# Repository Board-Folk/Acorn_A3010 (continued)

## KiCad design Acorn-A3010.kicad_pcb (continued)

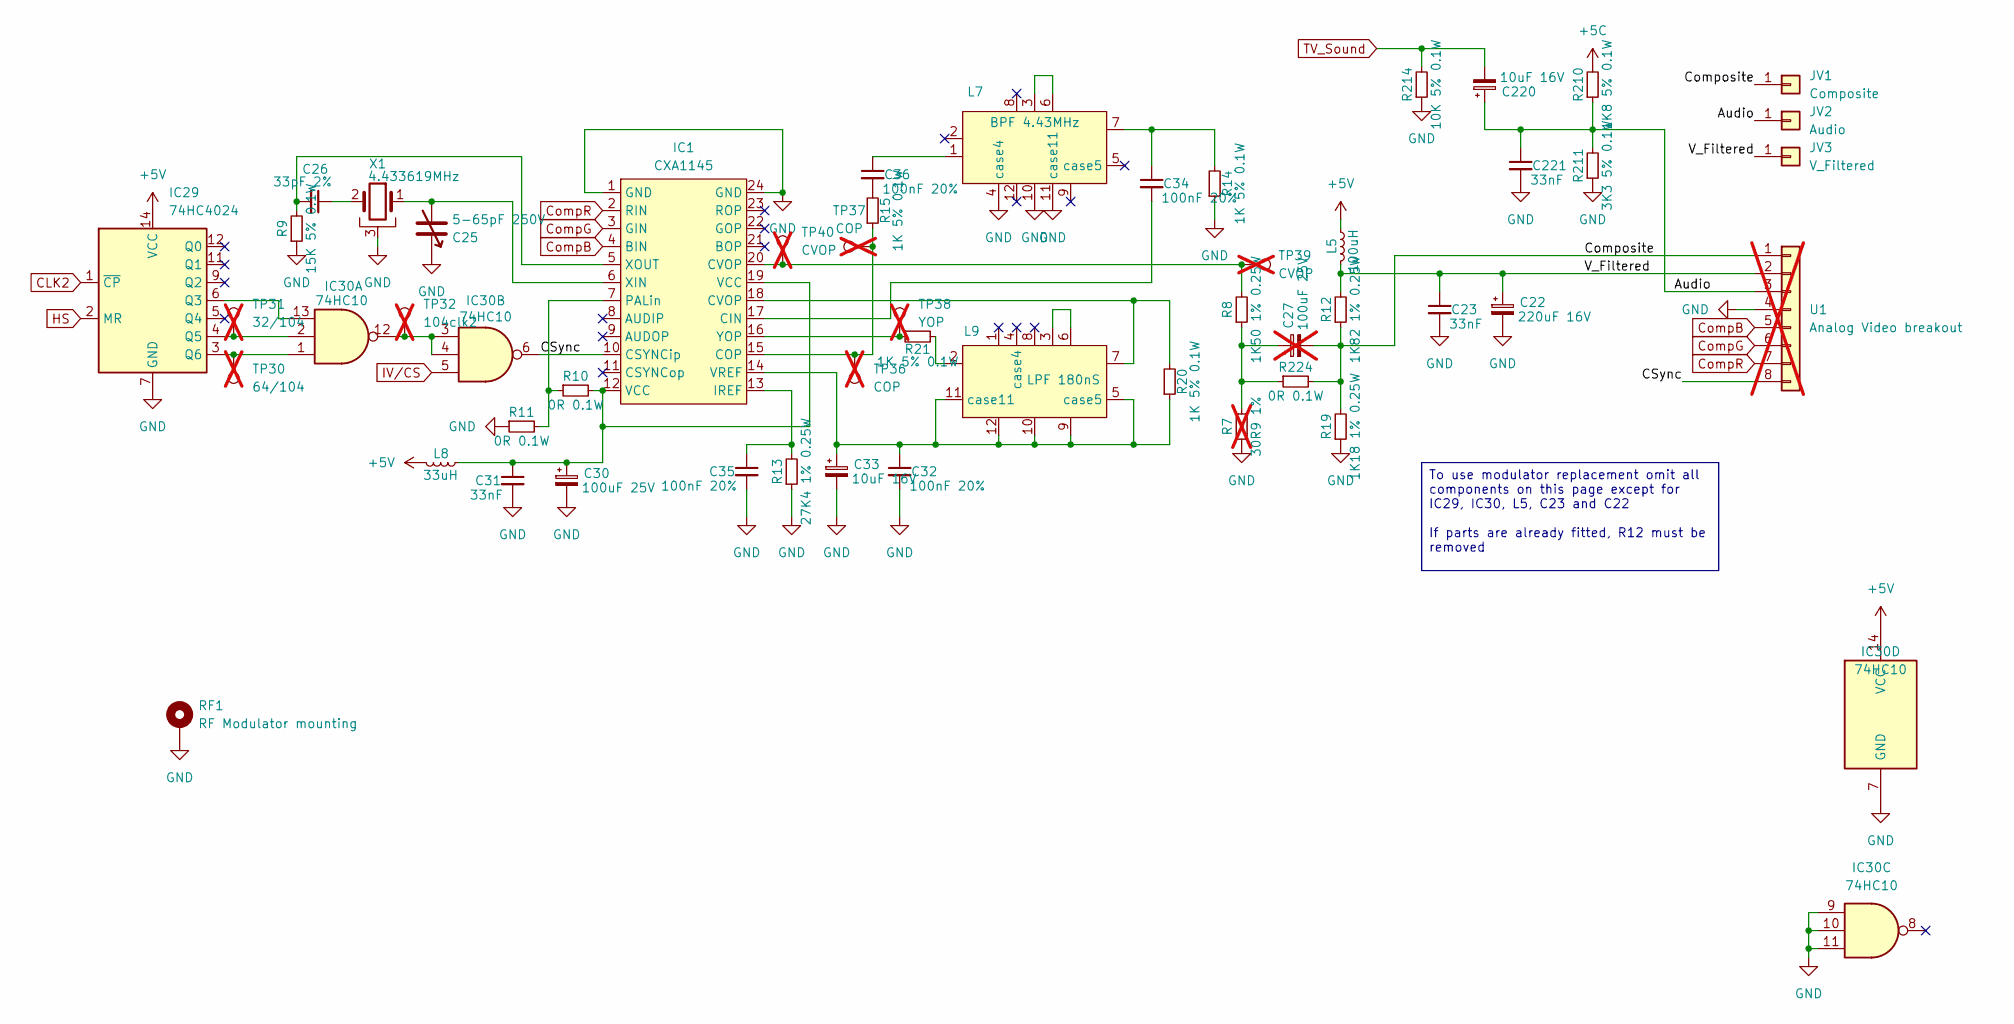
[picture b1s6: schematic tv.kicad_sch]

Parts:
C22: 220uF 16V; CP_Radial_D8.0mm_P5.00mm
C23, C31, C221: 33nF; C_0805_2012Metric; LCSC C344201
C25: 5-65pF 250V; Trim_Capacitor
C26: 33pF 2%; C_0805_2012Metric; LCSC C107115
C27: 100uF 25V; CP_Radial_Tantal_D6.0mm_P5.00mm; not fitted
C30: 100uF 25V; CP_Radial_D8.0mm_P5.00mm
C32, C34, C35, C36: 100nF 20%; C_0805_2012Metric; LCSC C49678
C33: 10uF 16V; CP_Radial_Tantal_D4.5mm_P5.00mm
C220: 10uF 16V; CP_Radial_D5.0mm_P2.50mm
IC1: CXA1145; SOJ-24_7.62x15.875mm_P1.27mm
IC29: 74HC4024; SOIC-14_3.9x8.7mm_P1.27mm; LCSC C2652991
IC30: 74HC10; SOIC-14_3.9x8.7mm_P1.27mm; LCSC C6816
JV1: Composite; PinHeader_1x01_P2.54mm_Vertical
JV2: Audio; PinHeader_1x01_P2.54mm_Vertical
JV3: V_Filtered; PinHeader_1x01_P2.54mm_Vertical
L5: 100uH; L_Axial_L6.6mm_D2.7mm_P10.16mm_Horizontal_Vishay_IM-2
L7: BPF 4.43MHz; BPF4_43M
L8: 33uH; L_Axial_L6.6mm_D2.7mm_P10.16mm_Horizontal_Vishay_IM-2
L9: LPF 180nS; LPF180nS
R7: 30R9 1%; R_1206_3216Metric; LCSC C2960740; not fitted
R8: 1K50 1% 0.25W; R_1206_3216Metric; LCSC C114929
R9: 15K 5% 0.1W; R_0805_2012Metric; LCSC C2933528
R10, R11, R224: 0R 0.1W; R_0805_2012Metric; LCSC C17477
R12: 1K82 1% 0.25W; R_1206_3216Metric; LCSC C844020
R13: 27K4 1% 0.25W; R_1206_3216Metric; LCSC C17477
R14, R15, R20, R21: 1K 5% 0.1W; R_0805_2012Metric; LCSC C2907232
R19: 1K18 1% 0.25W; R_1206_3216Metric; LCSC C422599
R210: 1K8 5% 0.1W; R_0805_2012Metric; LCSC C54102237
R211: 3K3 5% 0.1W; R_0805_2012Metric; LCSC C2930266
R214: 10K 5% 0.1W; R_0805_2012Metric; LCSC C2907219
RF1: RF Modulator mounting; Rf Modulator
TP30: 64/104; TestPoint_Pad_D1.0mm; not fitted
TP31: 32/104; TestPoint_Pad_D1.0mm; not fitted
TP32: 104clk2; TestPoint_Pad_D1.0mm; not fitted
TP36, TP37: COP; TestPoint_Pad_D1.0mm; not fitted
TP38: YOP; TestPoint_Pad_D1.0mm; not fitted
TP39, TP40: CVOP; TestPoint_Pad_D1.0mm; not fitted
U1: Analog Video breakout; PinSocket_1x08_P2.54mm_Vertical; not fitted
X1: 4.433619MHz; Crystal_HC49-U_Horizontal_1EP_style2

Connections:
+5C: R210.2; also elsewhere on the board
+5V: IC29.14 (VCC), IC30.14 (VCC), L5.1, L8.2; also elsewhere on the board
/Analog Video/Audio: C220.1, C221.1, JV2.1, R210.1, R211.2, U1.3
/Analog Video/CSync: IC1.10 (CSYNCip), IC30.6, U1.8
/Analog Video/Composite: C27.2, JV1.1, R12.1, R19.2, R224.2, U1.1
/Analog Video/V_Filtered: C22.1, C23.1, JV3.1, L5.2, R12.2, U1.2
CLK2: IC29.1 (~CP); also elsewhere on the board
CompB: IC1.4 (BIN), U1.5; also elsewhere on the board
CompG: IC1.3 (GIN), U1.6; also elsewhere on the board
CompR: IC1.2 (RIN), U1.7; also elsewhere on the board
GND: C22.2, C23.2, C25.1, C30.2, C31.2, C32.2, C33.2, C35.2, C221.2, IC1.1 (GND), IC1.24 (GND), IC29.7 (GND), IC30.7 (GND), IC30.9, IC30.10, IC30.11, L7.4 (case4), L7.10, L7.11 (case11), R7.1, R9.1, R11.1, R13.1, R14.1, R19.1, R211.1, R214.1, RF1.1, U1.4, X1.3; also elsewhere on the board
HS: IC29.2 (MR); also elsewhere on the board
IV/CS: IC30.5; also elsewhere on the board
unnamed: C26.1, X1.2
unnamed: C27.1, R7.2, R8.1, R224.1
unnamed: C30.1, C31.1, IC1.12 (VCC), IC1.19 (VCC), L8.1, R10.2
unnamed: C34.1, L7.7, R14.2
unnamed: C36.1, L7.1
unnamed: C36.2, R15.2
unnamed: C34.2, IC1.17 (CIN)
unnamed: IC1.15 (COP), R15.1, TP36.1, TP37.1
unnamed: IC1.18 (CVOP), L9.7, R20.2
unnamed: IC1.20 (CVOP), R8.2, TP39.1, TP40.1
unnamed: C35.1, IC1.13 (IREF), R13.2
unnamed: IC1.7 (PALin), R10.1, R11.2
unnamed: C32.1, C33.1, IC1.14 (VREF), L9.5 (case5), L9.9, L9.10, L9.11 (case11), L9.12, R20.1
unnamed: C25.2, IC1.6 (XIN), X1.1
unnamed: C26.2, IC1.5 (XOUT), R9.2
unnamed: IC1.16 (YOP), R21.1, TP38.1
unnamed: IC29.6 (Q3), IC30.13
unnamed: IC29.4 (Q5), IC30.2, TP31.1
unnamed: IC29.3 (Q6), IC30.1, TP30.1
unnamed: IC30.3, IC30.4, IC30.12, TP32.1
unnamed: L7.3, L7.6
unnamed: L9.2, R21.2
unnamed: L9.3, L9.6
TV_Sound: C220.2, R214.2; also elsewhere on the board

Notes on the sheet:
To use modulator replacement omit all components on this page except for IC29, IC30, L5, C23 and C22 If parts are already fitted, R12 must be removed

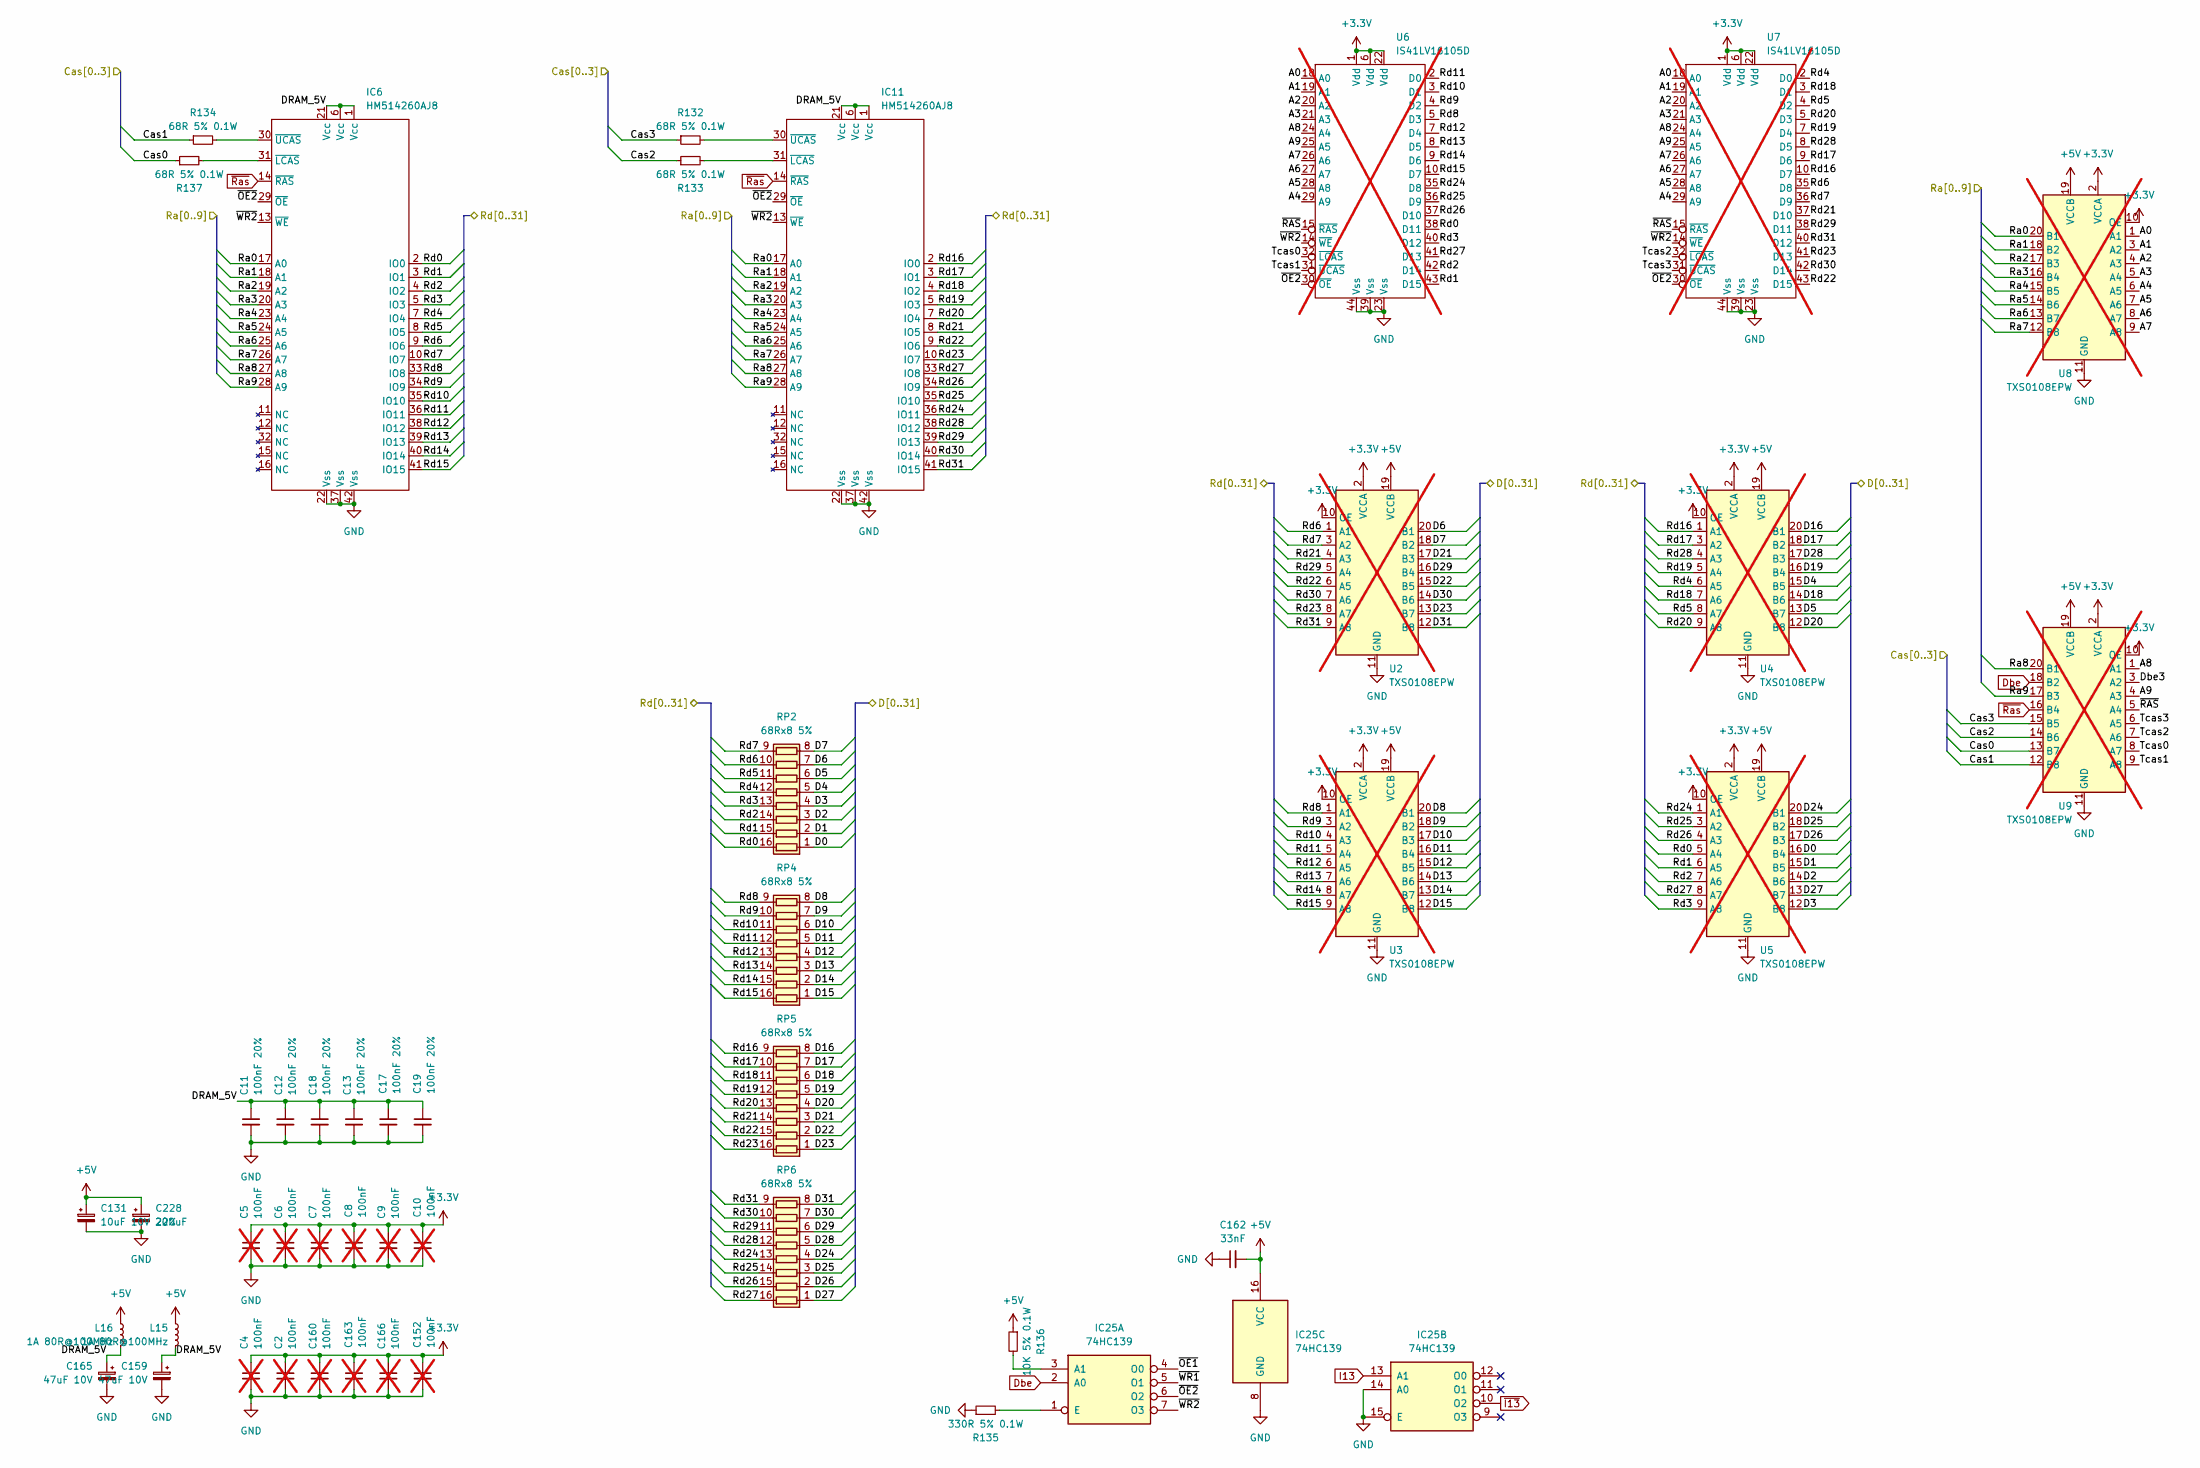
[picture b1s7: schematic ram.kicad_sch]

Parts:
C2, C4, C5, C6, C7, C8, C9, C10, C152, C160, C163, C166: 100nF; C_0805_2012Metric; LCSC C49678; not fitted
C11, C12, C13, C17, C18, C19: 100nF 20%; C_0805_2012Metric; LCSC C49678
C131: 10uF 10V 20%; CP_Radial_Tantal_D7.0mm_P5.00mm
C159, C165: 47uF 10V; CP_Axial_L11.0mm_D6.0mm_P18.00mm_Horizontal
C162: 33nF; C_0805_2012Metric; LCSC C49678
C228: 220uF; CP_Radial_D8.0mm_P5.00mm
IC6, IC11: HM514260AJ8; SOJ-42_10.16mm_P1.27mm
IC25: 74HC139; SOIC-16_3.9x9.9mm_P1.27mm; LCSC C7494
L15, L16: 1A 80R@100MHz; L_Acorn_8x3mm
R132, R133, R134, R137: 68R 5% 0.1W; R_0805_2012Metric
R135: 330R 5% 0.1W; R_0805_2012Metric; LCSC C17630
R136: 10K 5% 0.1W; R_0805_2012Metric; LCSC C2907219
RP2, RP4, RP5, RP6: 68Rx8 5%; SOIC-16W_5.3x10.2mm_P1.27mm; LCSC C1739978
U2, U3, U4, U5, U8, U9: TXS0108EPW; TSSOP-20_4.4x6.5mm_P0.65mm; LCSC C17206; not fitted
U6, U7: IS41LV16105D; TSOP-II-44-50; not fitted

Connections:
+5V: C131.1, C162.2, C228.1, IC25.16 (VCC), L15.1, L16.1, R136.1, U2.19 (VCCB), U3.19 (VCCB), U4.19 (VCCB), U5.19 (VCCB), U8.19 (VCCB), U9.19 (VCCB); also elsewhere on the board
/CPU/Cas0: R137.1, U9.13 (B7); also elsewhere on the board
/CPU/Cas1: R134.1, U9.12 (B8); also elsewhere on the board
/CPU/Cas2: R133.1, U9.14 (B6); also elsewhere on the board
/CPU/Cas3: R132.1, U9.15 (B5); also elsewhere on the board
/CPU/D0: RP2.1 (R1.1), U5.16 (B4); also elsewhere on the board
/CPU/D1: RP2.2 (R2.1), U5.15 (B5); also elsewhere on the board
/CPU/D2: RP2.3 (R3.1), U5.14 (B6); also elsewhere on the board
/CPU/D3: RP2.4 (R4.1), U5.12 (B8); also elsewhere on the board
/CPU/D4: RP2.5 (R5.1), U4.15 (B5); also elsewhere on the board
/CPU/D5: RP2.6 (R6.1), U4.13 (B7); also elsewhere on the board
/CPU/D6: RP2.7 (R7.1), U2.20 (B1); also elsewhere on the board
/CPU/D7: RP2.8 (R8.1), U2.18 (B2); also elsewhere on the board
/CPU/D8: RP4.8 (R8.1), U3.20 (B1); also elsewhere on the board
/CPU/D9: RP4.7 (R7.1), U3.18 (B2); also elsewhere on the board
/CPU/D10: RP4.6 (R6.1), U3.17 (B3); also elsewhere on the board
/CPU/D11: RP4.5 (R5.1), U3.16 (B4); also elsewhere on the board
/CPU/D12: RP4.4 (R4.1), U3.15 (B5); also elsewhere on the board
/CPU/D13: RP4.3 (R3.1), U3.14 (B6); also elsewhere on the board
/CPU/D14: RP4.2 (R2.1), U3.13 (B7); also elsewhere on the board
/CPU/D15: RP4.1 (R1.1), U3.12 (B8); also elsewhere on the board
/CPU/D16: RP5.8 (R8.1), U4.20 (B1); also elsewhere on the board
/CPU/D17: RP5.7 (R7.1), U4.18 (B2); also elsewhere on the board
/CPU/D18: RP5.6 (R6.1), U4.14 (B6); also elsewhere on the board
/CPU/D19: RP5.5 (R5.1), U4.16 (B4); also elsewhere on the board
/CPU/D20: RP5.4 (R4.1), U4.12 (B8); also elsewhere on the board
/CPU/D21: RP5.3 (R3.1), U2.17 (B3); also elsewhere on the board
/CPU/D22: RP5.2 (R2.1), U2.15 (B5); also elsewhere on the board
/CPU/D23: RP5.1 (R1.1), U2.13 (B7); also elsewhere on the board
/CPU/D24: RP6.4 (R4.1), U5.20 (B1); also elsewhere on the board
/CPU/D25: RP6.3 (R3.1), U5.18 (B2); also elsewhere on the board
/CPU/D26: RP6.2 (R2.1), U5.17 (B3); also elsewhere on the board
/CPU/D27: RP6.1 (R1.1), U5.13 (B7); also elsewhere on the board
/CPU/D28: RP6.5 (R5.1), U4.17 (B3); also elsewhere on the board
/CPU/D29: RP6.6 (R6.1), U2.16 (B4); also elsewhere on the board
/CPU/D30: RP6.7 (R7.1), U2.14 (B6); also elsewhere on the board
/CPU/D31: RP6.8 (R8.1), U2.12 (B8); also elsewhere on the board
/CPU/Ra0: IC6.17 (A0), IC11.17 (A0), U8.20 (B1); also elsewhere on the board
/CPU/Ra1: IC6.18 (A1), IC11.18 (A1), U8.18 (B2); also elsewhere on the board
/CPU/Ra2: IC6.19 (A2), IC11.19 (A2), U8.17 (B3); also elsewhere on the board
/CPU/Ra3: IC6.20 (A3), IC11.20 (A3), U8.16 (B4); also elsewhere on the board
/CPU/Ra4: IC6.23 (A4), IC11.23 (A4), U8.15 (B5); also elsewhere on the board
/CPU/Ra5: IC6.24 (A5), IC11.24 (A5), U8.14 (B6); also elsewhere on the board
/CPU/Ra6: IC6.25 (A6), IC11.25 (A6), U8.13 (B7); also elsewhere on the board
/CPU/Ra7: IC6.26 (A7), IC11.26 (A7), U8.12 (B8); also elsewhere on the board
/CPU/Ra8: IC6.27 (A8), IC11.27 (A8), U9.20 (B1); also elsewhere on the board
/CPU/Ra9: IC6.28 (A9), IC11.28 (A9), U9.17 (B3); also elsewhere on the board
/RAM/DRAM_5V: C11.1, C12.1, C13.1, C17.1, C18.1, C19.1, C159.1, C165.1, IC6.1 (Vcc), IC6.6 (Vcc), IC6.21 (Vcc), IC11.1 (Vcc), IC11.6 (Vcc), IC11.21 (Vcc), L15.2, L16.2
/RAM/Rd0: IC6.2 (IO0), RP2.16 (R1.2), U5.5 (A4), U6.38 (D11)
/RAM/Rd1: IC6.3 (IO1), RP2.15 (R2.2), U5.6 (A5), U6.43 (D15)
/RAM/Rd2: IC6.4 (IO2), RP2.14 (R3.2), U5.7 (A6), U6.42 (D14)
/RAM/Rd3: IC6.5 (IO3), RP2.13 (R4.2), U5.9 (A8), U6.40 (D12)
/RAM/Rd4: IC6.7 (IO4), RP2.12 (R5.2), U4.6 (A5), U7.2 (D0)
/RAM/Rd5: IC6.8 (IO5), RP2.11 (R6.2), U4.8 (A7), U7.4 (D2)
/RAM/Rd6: IC6.9 (IO6), RP2.10 (R7.2), U2.1 (A1), U7.35 (D8)
/RAM/Rd7: IC6.10 (IO7), RP2.9 (R8.2), U2.3 (A2), U7.36 (D9)
/RAM/Rd8: IC6.33 (IO8), RP4.9 (R8.2), U3.1 (A1), U6.5 (D3)
/RAM/Rd9: IC6.34 (IO9), RP4.10 (R7.2), U3.3 (A2), U6.4 (D2)
/RAM/Rd10: IC6.35 (IO10), RP4.11 (R6.2), U3.4 (A3), U6.3 (D1)
/RAM/Rd11: IC6.36 (IO11), RP4.12 (R5.2), U3.5 (A4), U6.2 (D0)
/RAM/Rd12: IC6.38 (IO12), RP4.13 (R4.2), U3.6 (A5), U6.7 (D4)
/RAM/Rd13: IC6.39 (IO13), RP4.14 (R3.2), U3.7 (A6), U6.8 (D5)
/RAM/Rd14: IC6.40 (IO14), RP4.15 (R2.2), U3.8 (A7), U6.9 (D6)
/RAM/Rd15: IC6.41 (IO15), RP4.16 (R1.2), U3.9 (A8), U6.10 (D7)
/RAM/Rd16: IC11.2 (IO0), RP5.9 (R8.2), U4.1 (A1), U7.10 (D7)
/RAM/Rd17: IC11.3 (IO1), RP5.10 (R7.2), U4.3 (A2), U7.9 (D6)
/RAM/Rd18: IC11.4 (IO2), RP5.11 (R6.2), U4.7 (A6), U7.3 (D1)
/RAM/Rd19: IC11.5 (IO3), RP5.12 (R5.2), U4.5 (A4), U7.7 (D4)
/RAM/Rd20: IC11.7 (IO4), RP5.13 (R4.2), U4.9 (A8), U7.5 (D3)
/RAM/Rd21: IC11.8 (IO5), RP5.14 (R3.2), U2.4 (A3), U7.37 (D10)
/RAM/Rd22: IC11.9 (IO6), RP5.15 (R2.2), U2.6 (A5), U7.43 (D15)
/RAM/Rd23: IC11.10 (IO7), RP5.16 (R1.2), U2.8 (A7), U7.41 (D13)
/RAM/Rd24: IC11.36 (IO11), RP6.13 (R4.2), U5.1 (A1), U6.35 (D8)
/RAM/Rd25: IC11.35 (IO10), RP6.14 (R3.2), U5.3 (A2), U6.36 (D9)
/RAM/Rd26: IC11.34 (IO9), RP6.15 (R2.2), U5.4 (A3), U6.37 (D10)
/RAM/Rd27: IC11.33 (IO8), RP6.16 (R1.2), U5.8 (A7), U6.41 (D13)
/RAM/Rd28: IC11.38 (IO12), RP6.12 (R5.2), U4.4 (A3), U7.8 (D5)
/RAM/Rd29: IC11.39 (IO13), RP6.11 (R6.2), U2.5 (A4), U7.38 (D11)
/RAM/Rd30: IC11.40 (IO14), RP6.10 (R7.2), U2.7 (A6), U7.42 (D14)
/RAM/Rd31: IC11.41 (IO15), RP6.9 (R8.2), U2.9 (A8), U7.40 (D12)
/RAM/~OE1: IC25.4 (O0)
/RAM/~OE2: IC6.29 (~OE), IC11.29 (~OE), IC25.6 (O2), U6.30 (~OE), U7.30 (~OE)
/RAM/~WR1: IC25.5 (O1)
/RAM/~WR2: IC6.13 (~WE), IC11.13 (~WE), IC25.7 (O3), U6.14 (~WE), U7.14 (~WE)
Dbe: IC25.2 (A0), U9.18 (B2); also elsewhere on the board
GND: C2.2, C4.2, C5.2, C6.2, C7.2, C8.2, C9.2, C10.2, C11.2, C12.2, C13.2, C17.2, C18.2, C19.2, C131.2, C152.2, C159.2, C160.2, C162.1, C163.2, C165.2, C166.2, C228.2, IC6.22 (Vss), IC6.37 (Vss), IC6.42 (Vss), IC11.22 (Vss), IC11.37 (Vss), IC11.42 (Vss), IC25.8 (GND), IC25.14 (A0), IC25.15 (E), R135.1, U2.11 (GND), U3.11 (GND), U4.11 (GND), U5.11 (GND), U6.23 (Vss), U6.39 (Vss), U6.44 (Vss), U7.23 (Vss), U7.39 (Vss), U7.44 (Vss), U8.11 (GND), U9.11 (GND); also elsewhere on the board
I13: IC25.13 (A1); also elsewhere on the board
unnamed: C2.1, C4.1, C5.1, C6.1, C7.1, C8.1, C9.1, C10.1, C152.1, C160.1, C163.1, C166.1, U2.2 (VCCA), U2.10 (OE), U3.2 (VCCA), U3.10 (OE), U4.2 (VCCA), U4.10 (OE), U5.2 (VCCA), U5.10 (OE), U6.1 (Vdd), U6.6 (Vdd), U6.22 (Vdd), U7.1 (Vdd), U7.6 (Vdd), U7.22 (Vdd), U8.2 (VCCA), U8.10 (OE), U9.2 (VCCA), U9.10 (OE)
unnamed: IC6.31 (~LCAS), R137.2
unnamed: IC6.30 (~UCAS), R134.2
unnamed: IC11.31 (~LCAS), R133.2
unnamed: IC11.30 (~UCAS), R132.2
unnamed: IC25.3 (A1), R136.2
unnamed: IC25.1 (E), R135.2
unnamed: U6.11 (NC), U6.12 (NC), U6.13 (NC), U6.16 (NC), U6.17 (NC), U6.33 (NC), U6.34 (NC)
unnamed: U6.15 (~RAS), U7.15 (~RAS), U9.5 (A4)
unnamed: U6.18 (A0), U7.18 (A0), U8.1 (A1)
unnamed: U6.19 (A1), U7.19 (A1), U8.3 (A2)
unnamed: U6.20 (A2), U7.20 (A2), U8.4 (A3)
unnamed: U6.21 (A3), U7.21 (A3), U8.5 (A4)
unnamed: U6.24 (A4), U7.24 (A4), U9.1 (A1)
unnamed: U6.25 (A5), U7.25 (A5), U9.4 (A3)
unnamed: U6.26 (A6), U7.26 (A6), U8.9 (A8)
unnamed: U6.27 (A7), U7.27 (A7), U8.8 (A7)
unnamed: U6.28 (A8), U7.28 (A8), U8.7 (A6)
unnamed: U6.29 (A9), U7.29 (A9), U8.6 (A5)
unnamed: U6.31 (~UCAS), U9.9 (A8)
unnamed: U6.32 (~LCAS), U9.8 (A7)
unnamed: U7.11 (NC), U7.12 (NC), U7.13 (NC), U7.16 (NC), U7.17 (NC), U7.33 (NC), U7.34 (NC)
unnamed: U7.31 (~UCAS), U9.6 (A5)
unnamed: U7.32 (~LCAS), U9.7 (A6)
~I13: IC25.10 (O2); also elsewhere on the board
~Ras: IC6.14 (~RAS), IC11.14 (~RAS), U9.16 (B4); also elsewhere on the board

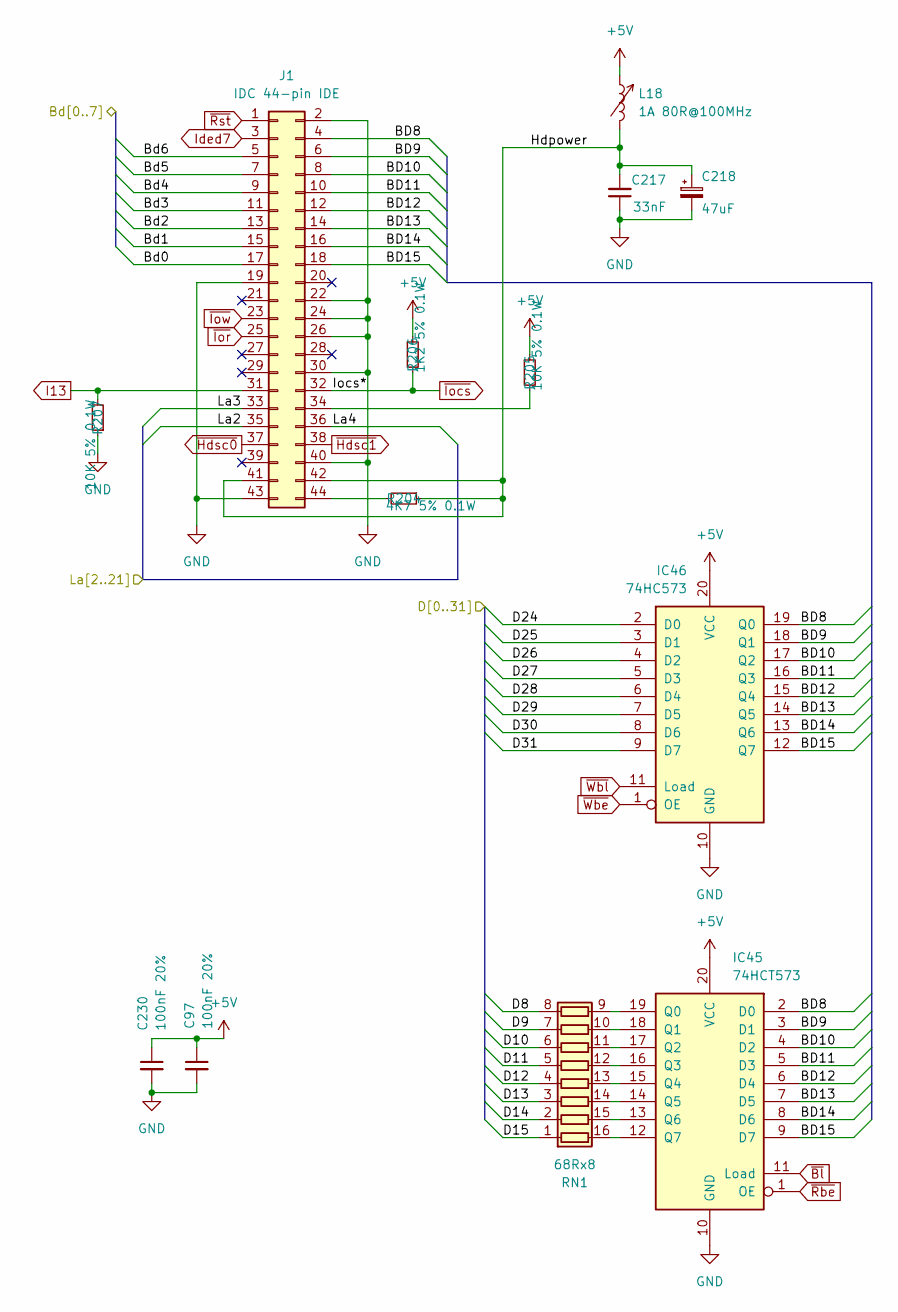
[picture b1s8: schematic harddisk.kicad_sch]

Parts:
C97, C230: 100nF 20%; C_0805_2012Metric; LCSC C49678
C217: 33nF; C_0805_2012Metric; LCSC C344201
C218: 47uF; CP_Radial_D8.0mm_P5.00mm
IC45: 74HCT573; SOP-20_7.5x12.8mm_P1.27mm; LCSC C52145555
IC46: 74HC573; SOP-20_7.5x12.8mm_P1.27mm; LCSC C55388
J1: IDC 44-pin IDE; PinHeader_2x22_P2.00mm_Vertical
L18: 1A 80R@100MHz; L_Acorn_8x3mm
R204: 4K7 5% 0.1W; R_0805_2012Metric; LCSC C2907326
R205: 10K 5% 0.1W; R_0805_2012Metric; LCSC C2907219
R206: 1K2 5% 0.1W; R_0805_2012Metric; LCSC C2933293
R207: 10K 5% 0.1W; R_0805_2012Metric
RN1: 68Rx8; SOIC-16W_5.3x10.2mm_P1.27mm; LCSC C1739978

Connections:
+5V: C97.1, C230.1, IC45.20 (VCC), IC46.20 (VCC), L18.1, R205.1, R206.1; also elsewhere on the board
/CPU/Bd0: J1.17; also elsewhere on the board
/CPU/Bd1: J1.15; also elsewhere on the board
/CPU/Bd2: J1.13; also elsewhere on the board
/CPU/Bd3: J1.11; also elsewhere on the board
/CPU/Bd4: J1.9; also elsewhere on the board
/CPU/Bd5: J1.7; also elsewhere on the board
/CPU/Bd6: J1.5; also elsewhere on the board
/CPU/D8: RN1.8 (R8.1); also elsewhere on the board
/CPU/D9: RN1.7 (R7.1); also elsewhere on the board
/CPU/D10: RN1.6 (R6.1); also elsewhere on the board
/CPU/D11: RN1.5 (R5.1); also elsewhere on the board
/CPU/D12: RN1.4 (R4.1); also elsewhere on the board
/CPU/D13: RN1.3 (R3.1); also elsewhere on the board
/CPU/D14: RN1.2 (R2.1); also elsewhere on the board
/CPU/D15: RN1.1 (R1.1); also elsewhere on the board
/CPU/D24: IC46.2 (D0); also elsewhere on the board
/CPU/D25: IC46.3 (D1); also elsewhere on the board
/CPU/D26: IC46.4 (D2); also elsewhere on the board
/CPU/D27: IC46.5 (D3); also elsewhere on the board
/CPU/D28: IC46.6 (D4); also elsewhere on the board
/CPU/D29: IC46.7 (D5); also elsewhere on the board
/CPU/D30: IC46.8 (D6); also elsewhere on the board
/CPU/D31: IC46.9 (D7); also elsewhere on the board
/CPU/La2: J1.35; also elsewhere on the board
/CPU/La3: J1.33; also elsewhere on the board
/CPU/La4: J1.36; also elsewhere on the board
/IDE Hard Disk/BD8: IC45.2 (D0), IC46.19 (Q0), J1.4
/IDE Hard Disk/BD9: IC45.3 (D1), IC46.18 (Q1), J1.6
/IDE Hard Disk/BD10: IC45.4 (D2), IC46.17 (Q2), J1.8
/IDE Hard Disk/BD11: IC45.5 (D3), IC46.16 (Q3), J1.10
/IDE Hard Disk/BD12: IC45.6 (D4), IC46.15 (Q4), J1.12
/IDE Hard Disk/BD13: IC45.7 (D5), IC46.14 (Q5), J1.14
/IDE Hard Disk/BD14: IC45.8 (D6), IC46.13 (Q6), J1.16
/IDE Hard Disk/BD15: IC45.9 (D7), IC46.12 (Q7), J1.18
/IDE Hard Disk/Hdpower: C217.2, C218.1, J1.41, J1.42, L18.2, R204.1
GND: C97.2, C217.1, C218.2, C230.2, IC45.10 (GND), IC46.10 (GND), J1.2, J1.19, J1.22, J1.24, J1.26, J1.30, J1.40, J1.43, R207.1; also elsewhere on the board
I13: J1.31, R207.2; also elsewhere on the board
Ided7: J1.3; also elsewhere on the board
unnamed: IC45.19 (Q0), RN1.9 (R8.2)
unnamed: IC45.18 (Q1), RN1.10 (R7.2)
unnamed: IC45.17 (Q2), RN1.11 (R6.2)
unnamed: IC45.16 (Q3), RN1.12 (R5.2)
unnamed: IC45.15 (Q4), RN1.13 (R4.2)
unnamed: IC45.14 (Q5), RN1.14 (R3.2)
unnamed: IC45.13 (Q6), RN1.15 (R2.2)
unnamed: IC45.12 (Q7), RN1.16 (R1.2)
unnamed: J1.34, R205.2
unnamed: J1.44, R204.2
~Bl: IC45.11 (Load); also elsewhere on the board
~Hdsc0: J1.37; also elsewhere on the board
~Hdsc1: J1.38; also elsewhere on the board
~Iocs: J1.32, R206.2; also elsewhere on the board
~Ior: J1.25; also elsewhere on the board
~Iow: J1.23; also elsewhere on the board
~Rbe: IC45.1 (OE); also elsewhere on the board
~Rst: J1.1; also elsewhere on the board
~Wbe: IC46.1 (OE); also elsewhere on the board
~Wbl: IC46.11 (Load); also elsewhere on the board

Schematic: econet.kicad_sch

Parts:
SK11: Econet; PinSocket_1x03_P2.54mm_Vertical

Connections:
~EFiq: SK11.3; also elsewhere on the board
~S2: SK11.1; also elsewhere on the board
~Wbe: SK11.2; also elsewhere on the board

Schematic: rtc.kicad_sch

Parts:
BT2: VARTA 2800 1V2 0.28Ah; Varta-2800; not fitted
C65: 12pF 2%; C_0805_2012Metric; LCSC C1792
C74: 4.7uF 16V; CP_Radial_D8.0mm_P5.00mm
C229: 33nF; C_0805_2012Metric; LCSC C344201
D15: BAS16; SOT-23-3
IC5: PCF8583; SOIC-8_7.5x5.85mm_P1.27mm
R60, R73: 180R 5% 0.1W; R_0805_2012Metric; LCSC C6639030
R61: 47R 5% 0.1W; R_0805_2012Metric; LCSC C2907268
R74, R75: 4K7 5% 0.1W; R_0805_2012Metric; LCSC C2907326
X2: 32.768KHz; Crystal_AT310_D3.0mm_L10.0mm_Horizontal_1EP_style2

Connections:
+5V: D15.1 (A), R74.2, R75.2; also elsewhere on the board
C0: IC5.5 (Sda), R75.1; also elsewhere on the board
C1: IC5.6 (Scl), R74.1; also elsewhere on the board
GND: C74.2, C229.1, IC5.3 (A0), IC5.4 (Vss), R73.1, X2.3; also elsewhere on the board
unnamed: BT2.1 (+), R60.1
unnamed: BT2.2 (-), R73.2
unnamed: D15.3 (K), R60.2, R61.2
unnamed: C65.2, IC5.1 (OSCi), X2.1
unnamed: IC5.2 (OSCo), X2.2
unnamed: C65.1, C74.1, C229.2, IC5.8 (Vcc), R61.1

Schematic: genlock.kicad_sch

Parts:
IC8: 74HCT14; SOIC-14_3.9x8.7mm_P1.27mm; LCSC C6769
LK6: Conn_02x04_Odd_Even; PinHeader_2x04_P2.54mm_Vertical

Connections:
Clkvid: LK6.5; also elsewhere on the board
GND: LK6.3, LK6.8; also elsewhere on the board
HS: IC8.3; also elsewhere on the board
IV/CS: IC8.6, LK6.1; also elsewhere on the board
unnamed: IC8.4, LK6.2
Vidclk: LK6.6; also elsewhere on the board
V/CS: IC8.5; also elsewhere on the board
sink: LK6.4; also elsewhere on the board
~Sup: LK6.7; also elsewhere on the board

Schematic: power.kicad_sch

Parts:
C14, C16, C28: 47uF 16V; CP_Radial_D8.0mm_P5.00mm
C20, C21: 1uF; C_0805_2012Metric; LCSC Part C77083; not fitted
C24, C29, C37, C38, C40, C50, C64, C66, C67, C70, C71, C85, C91, C92, C95, C103, C107, C109, C116, C117, C138, C151, C222, C223, C227: 33nF; C_0805_2012Metric; LCSC C344201
C39, C49, C110, C161: 220uF 16V; CP_Radial_D8.0mm_P5.00mm
C59, C83: 10uF 10V 20%; CP_Radial_Tantal_D8.0mm_P5.00mm
C106: 47uF 10V 20%; CP_Radial_Tantal_D9.0mm_P5.00mm
FS1: Fuse 1A; Fuseholder_Clip-5x20mm_Bel_FC-203-22_Lateral_P17.80x5.00mm_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
L6, L13: 1A 80R@100MHz; L_Acorn_8x3mm
LK13: RFI GND; Link_Connected
MW1: RPT-60B; RPT-60_cutout
PL1: Mains Input; AC_Power_Header
PL2: 0V; Molex_19708-4003
PL3: Earth; Molex_19708-4003
PL4: +5V; Molex_19708-4003
PL5: FDD Power; Molex_KK-254_AE-6410-04A_1x04_P2.54mm_Vertical
SW2: SW_DPST; Power_Switch
TP2: +12V; PinHeader_1x01_P2.54mm_Vertical; not fitted
TP3: -12V; PinHeader_1x01_P2.54mm_Vertical; not fitted
U10: ZLDO1117G33TA; SOT-223-3_TabPin2; LCSC C18212698; not fitted

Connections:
+5C: C70.2, C106.1, C107.2, C109.2, L13.1; also elsewhere on the board
+5V: C20.1, C24.2, C37.2, C38.2, C39.1, C40.2, C49.1, C50.2, C59.1, C64.2, C66.2, C67.2, C71.2, C83.1, C85.2, C91.2, C92.2, C95.2, C103.2, C110.1, C138.2, C151.2, C161.1, C227.2, FS1.2, L6.1, L13.2, PL4.1, U10.3 (IN); also elsewhere on the board
+12V: C14.1, C117.2, C222.2, MW1.7 (+12V), TP2.1; also elsewhere on the board
-12V: C16.2, C116.1, C223.1, MW1.8 (-12V), TP3.1; also elsewhere on the board
/Power/AC_L: PL1.2, SW2.4
/Power/AC_N: PL1.1, SW2.2
/Power/AC_SW_L: MW1.1 (AC/L), SW2.3
/Power/AC_SW_N: MW1.2 (AC/N), SW2.1
Earth: LK13.1
GND: C14.2, C16.1, C20.2, C21.2, C24.1, C28.2, C29.1, C37.1, C38.1, C39.2, C40.1, C49.2, C50.1, C59.2, C64.1, C66.1, C67.1, C70.1, C71.1, C83.2, C85.1, C91.1, C92.1, C95.1, C103.1, C106.2, C107.1, C109.1, C110.2, C116.2, C117.1, C138.1, C151.1, C161.2, C222.1, C223.2, C227.1, MW1.5 (GND), MW1.6 (GND), PL2.1, PL3.1, PL5.2, PL5.3, U10.1; also elsewhere on the board
unnamed: C21.1, U10.2 (OUT)
unnamed: FS1.1, MW1.3 (+5V), MW1.4 (+5V)
unnamed: C28.1, C29.2, L6.2, PL5.4
SndVSS: LK13.2; also elsewhere on the board
